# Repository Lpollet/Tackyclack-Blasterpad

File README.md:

The Tackyclack Blasterpad is a 5x5+5x1 pseudo-ortho gaming-focused keypad!

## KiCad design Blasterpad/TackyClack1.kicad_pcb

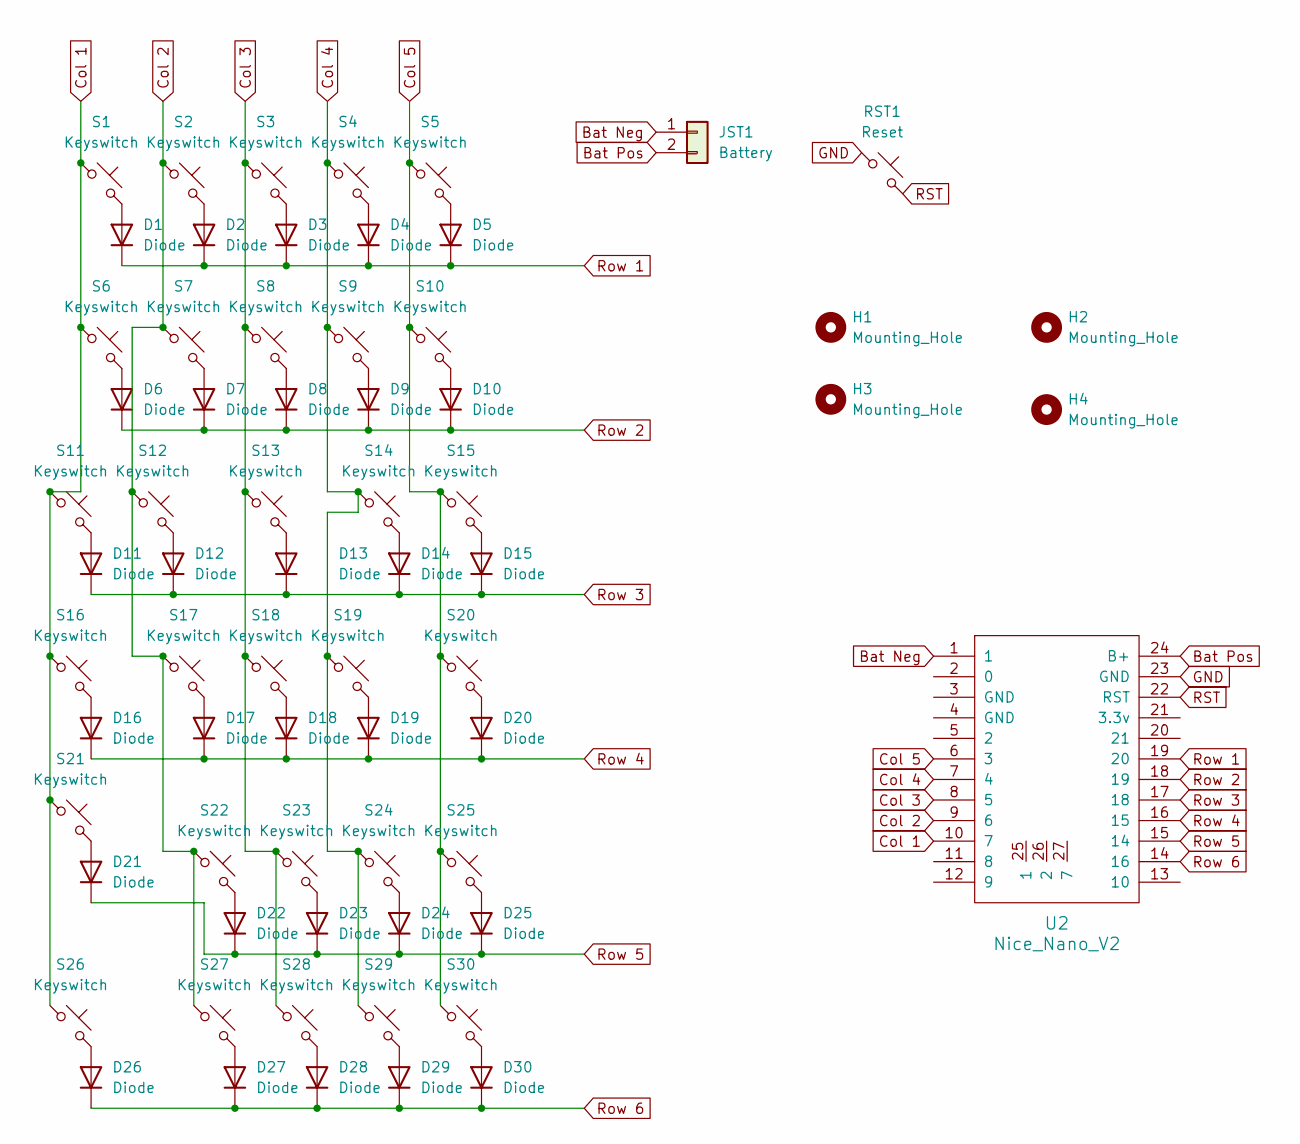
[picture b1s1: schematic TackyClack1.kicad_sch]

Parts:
D1, D2, D3, D4, D5, D6, D7, D8, D9, D10, D11, D12, D13, D14, D15, D16, D17, D18, D19, D20, D21, D22, D23, D24, D25, D26, D27, D28, D29, D30: Diode; Diode_DO-35
H1, H2, H3, H4: Mounting_Hole; MountingHole_4.5mm
JST1: Battery; JST_PH_S2B-PH-SM4-TB_1x02-1MP_P2.00mm_Horizontal
RST1: Reset; Button_TL3342
S1, S2, S3, S4, S5, S6, S7, S8, S9, S10, S12, S13, S14, S17, S18, S19, S22, S23, S24: Keyswitch; Hotswap_MX_1.00u
S11, S15, S16, S20, S21, S25: Keyswitch; Hotswap_MX_1.50u
S26, S27, S28, S29, S30: Keyswitch; Hotswap_Choc_V1_1.00u
U2: Nice_Nano_V2

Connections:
Bat Neg: JST1.1, U2.1
Bat Pos: JST1.2, U2.24 (B+)
Col 1: S1.1, S6.1, S11.1, S16.1, S21.1, S26.1, U2.10 (7)
Col 2: S2.1, S7.1, S12.1, S17.1, S22.1, S27.1, U2.9 (6)
Col 3: S3.1, S8.1, S13.1, S18.1, S23.1, S28.1, U2.8 (5)
Col 4: S4.1, S9.1, S14.1, S19.1, S24.1, S29.1, U2.7 (4)
Col 5: S5.1, S10.1, S15.1, S20.1, S25.1, S30.1, U2.6 (3)
GND: RST1.1, U2.23 (GND)
unnamed: D1.2 (A), S1.2
unnamed: D2.2 (A), S2.2
unnamed: D3.2 (A), S3.2
unnamed: D4.2 (A), S4.2
unnamed: D5.2 (A), S5.2
unnamed: D6.2 (A), S6.2
unnamed: D7.2 (A), S7.2
unnamed: D8.2 (A), S8.2
unnamed: D9.2 (A), S9.2
unnamed: D10.2 (A), S10.2
unnamed: D11.2 (A), S11.2
unnamed: D12.2 (A), S12.2
unnamed: D13.2 (A), S13.2
unnamed: D14.2 (A), S14.2
unnamed: D15.2 (A), S15.2
unnamed: D16.2 (A), S16.2
unnamed: D17.2 (A), S17.2
unnamed: D18.2 (A), S18.2
unnamed: D19.2 (A), S19.2
unnamed: D20.2 (A), S20.2
unnamed: D21.2 (A), S21.2
unnamed: D22.2 (A), S22.2
unnamed: D23.2 (A), S23.2
unnamed: D24.2 (A), S24.2
unnamed: D25.2 (A), S25.2
unnamed: D26.2 (A), S26.2
unnamed: D27.2 (A), S27.2
unnamed: D28.2 (A), S28.2
unnamed: D29.2 (A), S29.2
unnamed: D30.2 (A), S30.2
RST: RST1.2, U2.22 (RST)
Row 1: D1.1 (K), D2.1 (K), D3.1 (K), D4.1 (K), D5.1 (K), U2.19 (20)
Row 2: D6.1 (K), D7.1 (K), D8.1 (K), D9.1 (K), D10.1 (K), U2.18 (19)
Row 3: D11.1 (K), D12.1 (K), D13.1 (K), D14.1 (K), D15.1 (K), U2.17 (18)
Row 4: D16.1 (K), D17.1 (K), D18.1 (K), D19.1 (K), D20.1 (K), U2.16 (15)
Row 5: D21.1 (K), D22.1 (K), D23.1 (K), D24.1 (K), D25.1 (K), U2.15 (14)
Row 6: D26.1 (K), D27.1 (K), D28.1 (K), D29.1 (K), D30.1 (K), U2.14 (16)

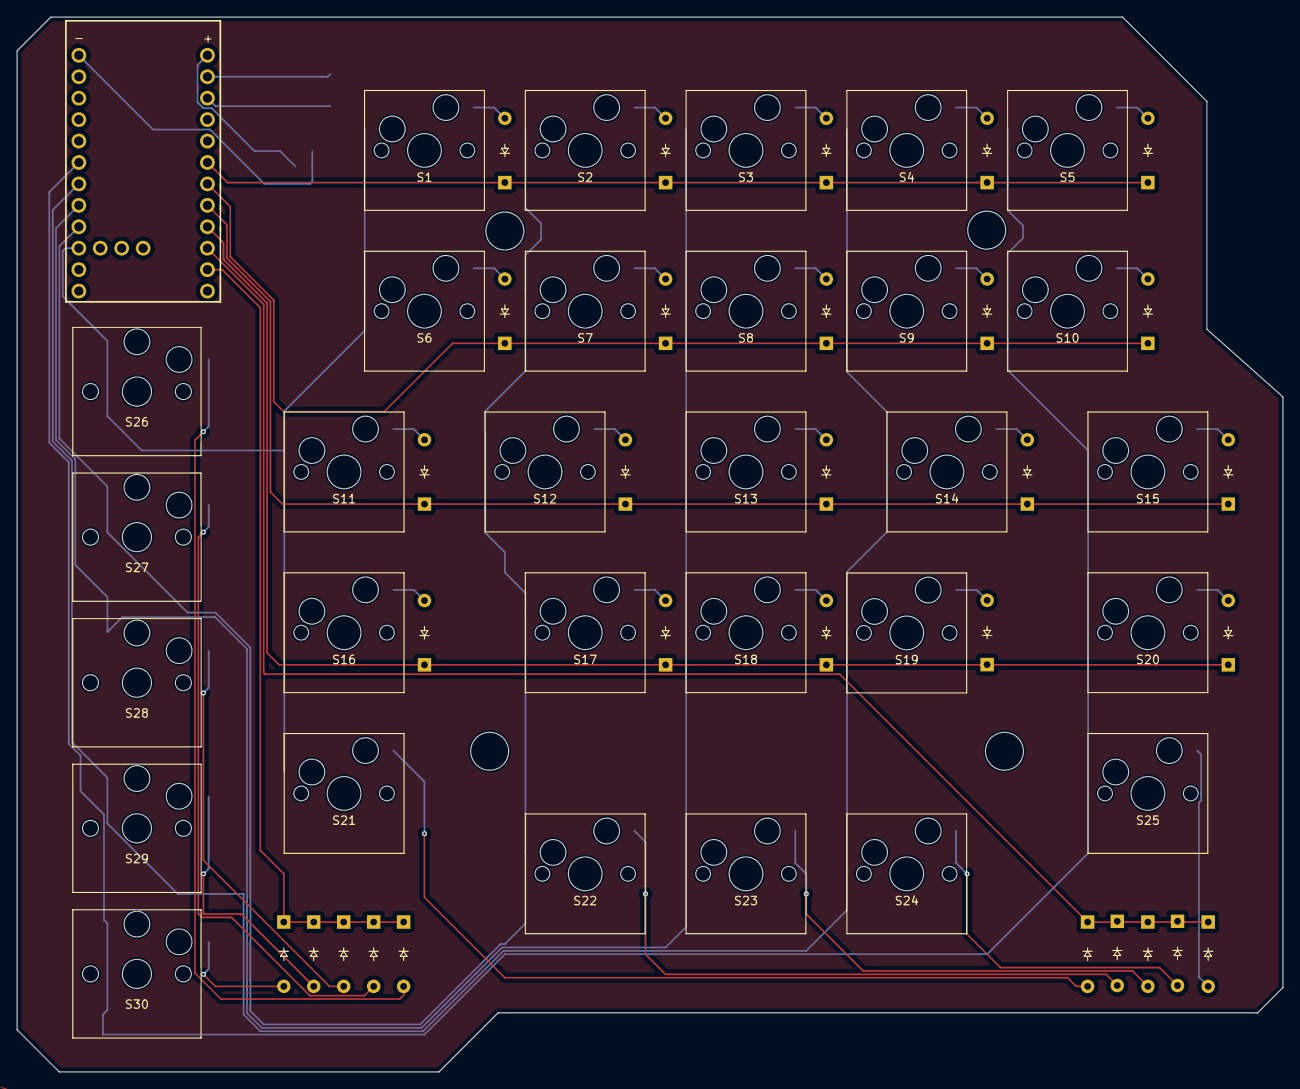
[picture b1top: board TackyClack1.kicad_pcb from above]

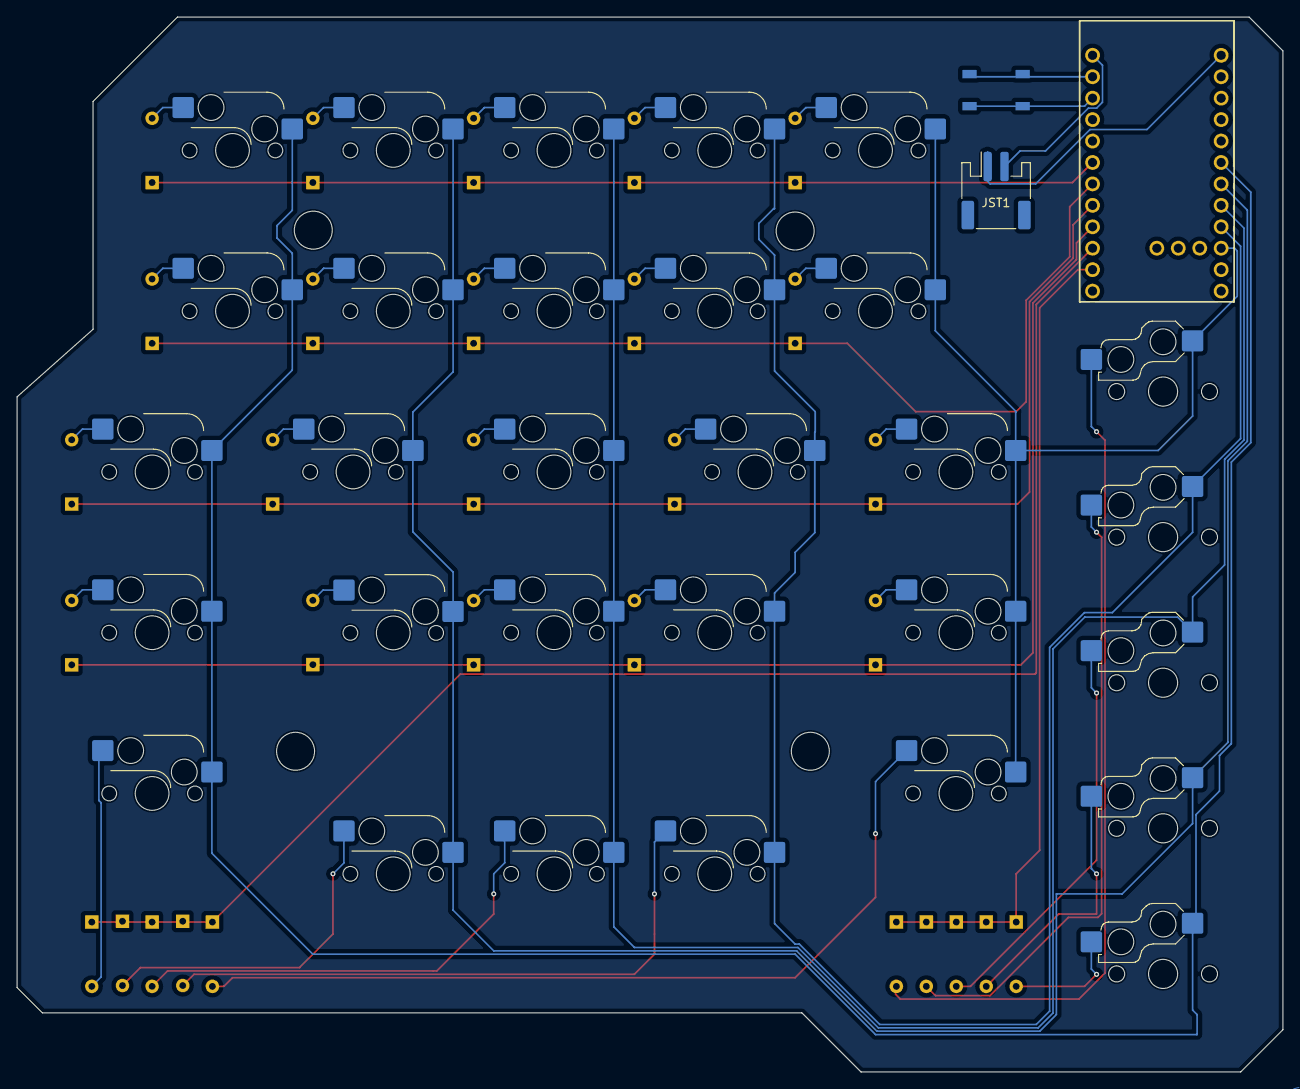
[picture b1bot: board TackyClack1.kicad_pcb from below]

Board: 2 copper layers, 150.0 x 125.0 mm, 67 parts (2 on the bottom side), 45 nets.
